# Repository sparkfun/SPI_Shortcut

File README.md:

SPI Shortcut
============
[  
*SPI Shortcut (TOL-09235)*](https://www.sparkfun.com/products/9235)

The SPI Shortcut allows you to control SPI pins over USB, allowing for a virtual "SPI Terminal". You will need to download the FTDI drivers
from [here](http://www.ftdichip.com/FTDrivers.htm). 

Repository Contents
-------------------
* **/Firmware** - The firmware that ships on the SPI Shortcut 
* **/Hardware** - All Eagle design files (.brd, .sch)

License Information
-------------------
The hardware is released under [Creative Commons Share-alike 3.0](http://creativecommons.org/licenses/by-sa/3.0/).  
All other code is open source so please feel free to do anything you want with it; you buy me a beer if you use this and we meet someday ([Beerware license](http://en.wikipedia.org/wiki/Beerware)).

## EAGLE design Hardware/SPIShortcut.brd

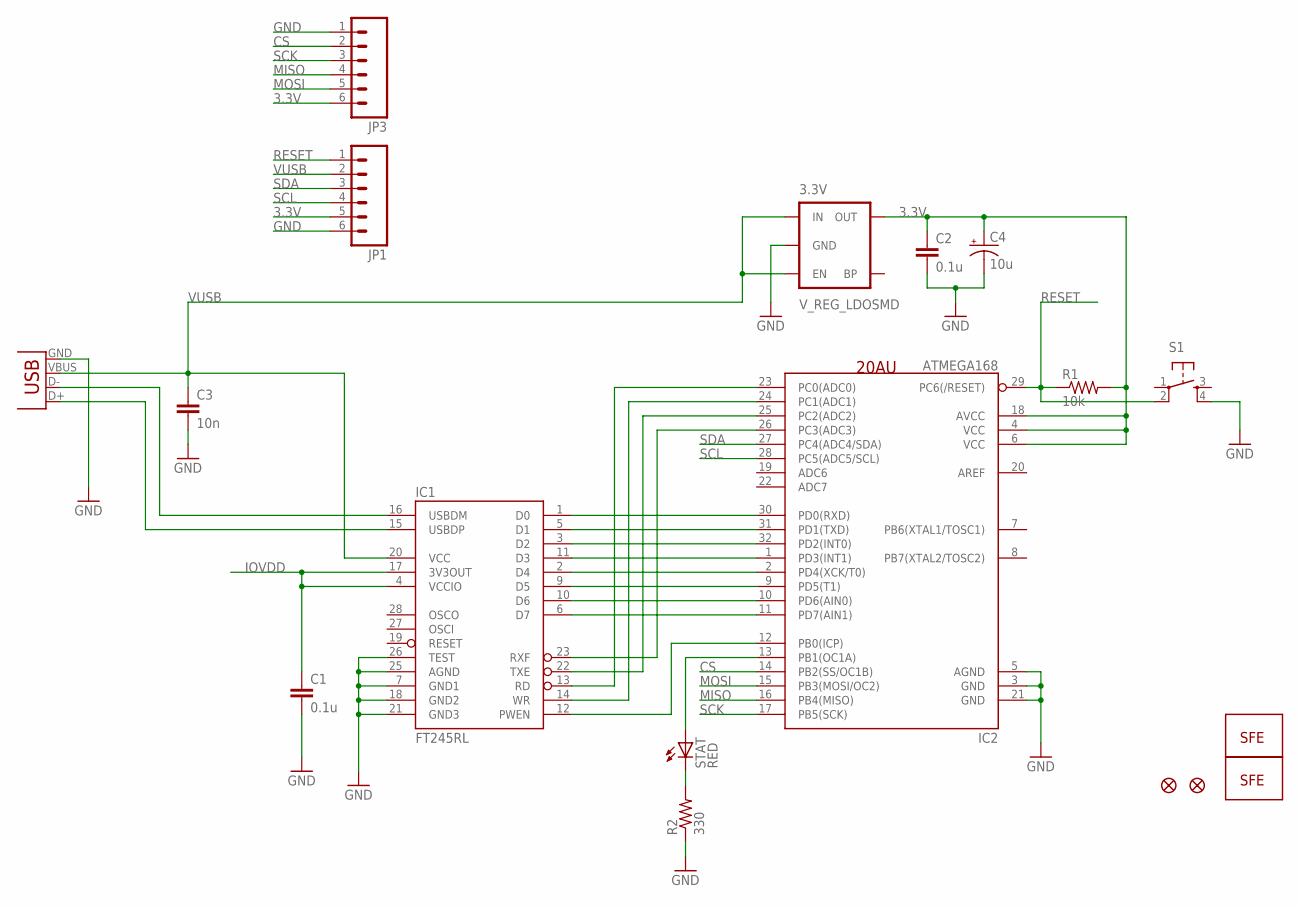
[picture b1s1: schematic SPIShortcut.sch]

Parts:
3.3V: V_REG_LDOSMD; SOT23-5
C1, C2: 0.1u; 0402-CAP
C3: 10n; 0402-CAP
C4: 10u; EIA3216
IC1: FT245RL; SSOP28DB
IC2: ATMEGA168; TQFP32-08
JP1, JP3: M06SIP; 1X06
R1: 10k; 0402-RES
R2: 330; 0402-RES
S1: TAC_SWITCHSMD; TACTILE_SWITCH_SMD
STAT: RED; LED-0603
U$3: LOGO-SFENEW; SFE-NEW-WEBLOGO
U$5, U$6: FIDUCIAL1X2; FIDUCIAL-1X2
U$7: LOGO-SFESK; SFE-LOGO-FLAME
X1: USBSMD; USB-MINIB

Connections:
3.3V: 3.3V.5 (OUT), C2.1, C4.A (+), IC2.4 (VCC), IC2.6 (VCC), IC2.18 (AVCC), JP1.5, JP3.6, R1.2
CS: IC2.14 (PB2(SS/OC1B)), JP3.2
GND: 3.3V.2 (GND), C1.2, C2.2, C3.2, C4.C (-), IC1.7 (GND1), IC1.18 (GND2), IC1.21 (GND3), IC1.25 (AGND), IC1.26 (TEST), IC2.3 (GND), IC2.5 (AGND), IC2.21 (GND), JP1.6, JP3.1, R2.1, S1.4, X1.GND
IOVDD: C1.1, IC1.4 (VCCIO), IC1.17 (3V3OUT)
MISO: IC2.16 (PB4(MISO)), JP3.4
MOSI: IC2.15 (PB3(MOSI/OC2)), JP3.5
unnamed: IC1.1 (D0), IC2.30 (PD0(RXD))
unnamed: IC1.5 (D1), IC2.31 (PD1(TXD))
unnamed: IC1.3 (D2), IC2.32 (PD2(INT0))
unnamed: IC1.11 (D3), IC2.1 (PD3(INT1))
unnamed: IC1.2 (D4), IC2.2 (PD4(XCK/T0))
unnamed: IC1.9 (D5), IC2.9 (PD5(T1))
unnamed: IC1.10 (D6), IC2.10 (PD6(AIN0))
unnamed: IC1.6 (D7), IC2.11 (PD7(AIN1))
unnamed: IC1.23 (RXF), IC2.26 (PC3(ADC3))
unnamed: IC1.16 (USBDM), X1.D-
unnamed: IC1.15 (USBDP), X1.D+
unnamed: IC1.22 (TXE), IC2.25 (PC2(ADC2))
unnamed: IC1.14 (WR), IC2.24 (PC1(ADC1))
unnamed: IC1.13 (RD), IC2.23 (PC0(ADC0))
unnamed: IC1.12 (PWEN), IC2.12 (PB0(ICP))
unnamed: IC2.13 (PB1(OC1A)), STAT.A
unnamed: R2.2, STAT.C
RESET: IC2.29 (PC6(/RESET)), JP1.1, R1.1, S1.2
SCK: IC2.17 (PB5(SCK)), JP3.3
SCL: IC2.28 (PC5(ADC5/SCL)), JP1.4
SDA: IC2.27 (PC4(ADC4/SDA)), JP1.3
VUSB: 3.3V.1 (IN), 3.3V.3 (EN), C3.1, IC1.20 (VCC), JP1.2, X1.VBUS

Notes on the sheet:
20AU

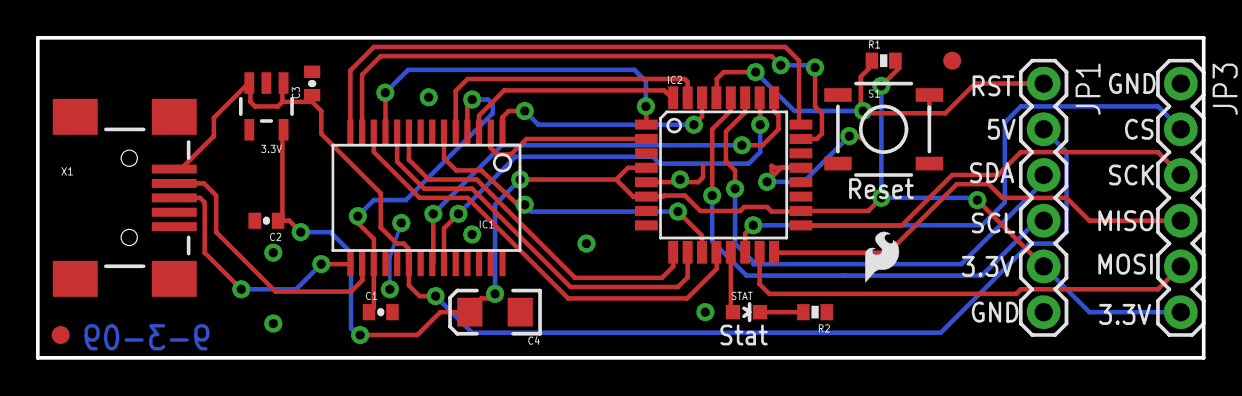
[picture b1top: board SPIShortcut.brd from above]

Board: 2 copper layers, 64.8 x 17.8 mm, 18 parts (1 on the bottom side), 28 nets.

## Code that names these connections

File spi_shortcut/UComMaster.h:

//*******************************************************
//
//		   SPI Shortcut Pin Definitions 
//				SparkFun Electronics
//   		   Written By Chris Taylor
//			
//*******************************************************
//HARDWARE NOTE: High Fuse should be set to 0xDF
//				 Low Fuse should be set to 0xFF

//*******************************************************
//					General Definitions
//*******************************************************
#define HOLD_TIME	20
#define OK	1
#define ERROR	0

#define CS		PB2
#define MOSI	PB3
#define MISO 	PB4
#define SCK		PB5

#define LED		PB1

#define SCL 	PC5
#define SDA		PC4


//*******************************************************
//					ATmega168 Pin Definitions
//*******************************************************

#define sbi(var, mask)   ((var) |= (uint8_t)(1 << mask))
#define cbi(var, mask)   ((var) &= (uint8_t)~(1 << mask))

//SPI Communication Pins
#define SPI_SCLK	5
#define SPI_IN		4
#define SPI_OUT		3
#define SPI_CS		2

//FT245 Control Pin Definitions
#define PWREN	(1<<0) //PB0 (Input to AVR)
#define RD		(1<<0) //PC0 (Output from AVR)
#define WR		(1<<1) //PC1 (Output from AVR)
#define TXE		(1<<2) //PC2 (Input to AVR)
#define RXF		(1<<3) //PC3 (Input to AVR)

//FT245 Data Pins (These pins switch between being I/O)
#define D0		(1<<0) //PD0
#define D1		(1<<1) //PD1
#define D2		(1<<2) //PD2
#define D3		(1<<3) //PD3
#define D4		(1<<4) //PD4
#define D5		(1<<5) //PD5
#define D6		(1<<6) //PD6
#define D7		(1<<7) //PD7

//*******************************************************
//					Global Macros
//*******************************************************
#define sbi(var, mask)   ((var) |= (uint8_t)(1 << mask))
#define cbi(var, mask)   ((var) &= (uint8_t)~(1 << mask))

//Macros for interfacing with the FT245
#define USBreadAllowed()	(PINC & RXF) != RXF
#define USBwriteAllowed()  	(PINC & TXE) != TXE
#define USBConfigured() 	(PINB & PWREN) != PWREN
#define setRD()		PORTC |= RD;
#define clearRD()	PORTC &= ~RD;
#define setWR()		PORTC |= WR;
#define clearWR()	PORTC &= ~WR;

//*******************************************************
//					Global Functions
//*******************************************************
void delay_ms(uint16_t x); // general purpose delay
void delay_micro(uint16_t x); // general purpose delay
void fill16(volatile uint8_t* src, uint8_t fill);
void fillFrame(volatile uint8_t* src, uint8_t fill);
void newcolor(uint8_t * r, uint8_t * g, uint8_t * b);
void clock_byte(volatile uint16_t my_byte, volatile uint8_t rowNum);
void ioinit (void);      // initializes IO
void setDataOutputs(void);
void setDataInputs(void);
void printf245(const char *text, ...);
char getchar245(void);
void reverse(char s[]);
void itoa2(int n, char s[]);
void parseCommand(void);
void executeCommand(void);
char string_compare(const char *search_string, const char *find_string);
void ascii2hex(volatile char *ascii_string);
void setPixel(int board, int offset, char r, char g, char b);
void setBoard(char r, char g, char b);
void sendButtonValues(void);
unsigned char read_from_EEPROM(unsigned int Address);
void write_to_EEPROM(unsigned int Address, unsigned char Data);

//*******************************************************
//					Structure Definitions
//*******************************************************
typedef struct{
	char ID;
	char Parameters[14];
	//char Checksum;
} Packet;

//*******************************************************
//					my_printf definitions 
//*******************************************************
#define MAIN_MENU 0
#define ARROW 1
#define INVALID 2
#define SEND_SINGLE 3 
#define ACTIONS_MENU 4
#define CONT_RECEIVE 5
#define SEND_COMMAND 6
#define CS_HIGH 7
#define CS_LOW 8 
#define STRING_SENT 9
#define SETTINGS 10
#define SET_POLARITY_1 11
#define SET_POLARITY_2 12
#define SET_POLARITY_3 13
#define MODE_CHANGED 14
#define FREQUENCY_MENU_1 15
#define FREQUENCY_MENU_2 16
#define FREQUENCY_CHANGED 17
#define DORDER_MENU 18
#define DORDER_CHANGED 19
#define CURRENT_SETTINGS 20
#define DATA_ORDER 21
#define MSB 22
#define LSB 23
#define DELAY 24
#define SETTINGS_CORRUPT 25

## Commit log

2013-08-16 Initial Release.
2013-08-16 Delete SPIShortcutDatasheet.odt
    No reason for this to be here.
2013-08-22 v1.0
2013-08-22 Initial commit of v16 files
2013-08-22 Matching official directory structure.
2013-08-22 Matching official structure, take 2.
2013-08-22 Fix delay, start to add TWI.
2013-08-22 Closer match.
2013-08-22 More directory fixups.
2013-10-09 Partial TWI and Saved String support
2013-12-22 Eliminate buffer overflow, change buffer to 200 bytes. Add "const" to all progmem variables to eliminate compiler warnings.
2013-12-22 Eliminate 1ms/char delay.
2013-12-23 Save settings to eeprom.
